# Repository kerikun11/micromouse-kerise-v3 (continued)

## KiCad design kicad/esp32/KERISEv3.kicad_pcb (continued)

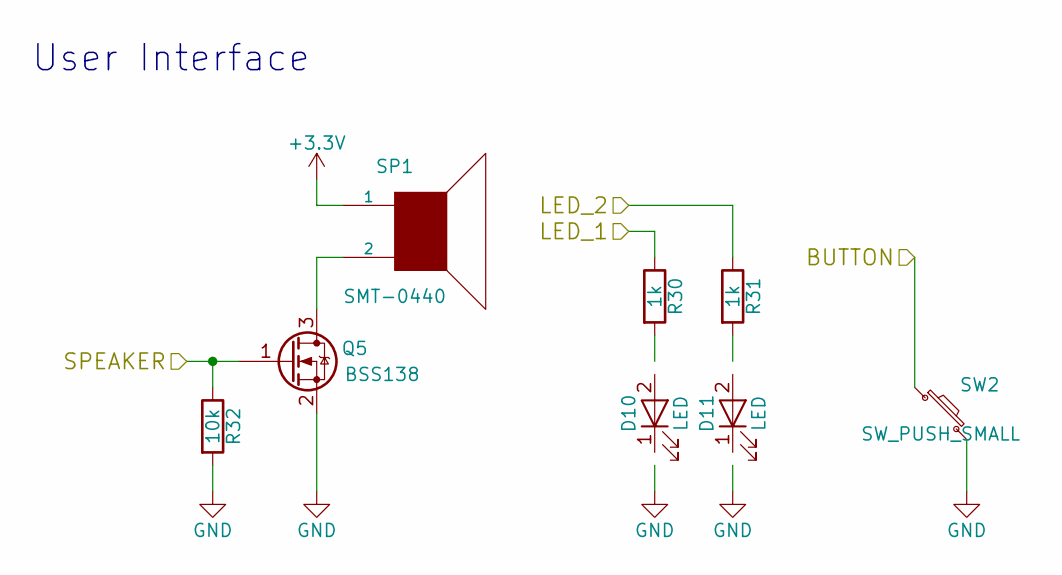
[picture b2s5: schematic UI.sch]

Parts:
D10, D11: LED; LED_0402
Q5: BSS138; SOT-23
R30, R31: 1k; R_0201
R32: 10k; R_0201
SP1: SMT-0440; SMT-0440-S-R
SW2: SW_PUSH_SMALL; SW_SPST_KMR2

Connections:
+3V3: SP1.1; also elsewhere on the board
BUTTON: SW2.1; also elsewhere on the board
GND: Q5.2 (S), R32.2, SW2.2; also elsewhere on the board
unnamed: Q5.1 (G), R32.1
unnamed 80: Q5.3 (D), SP1.2; also elsewhere on the board

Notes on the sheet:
User Interface

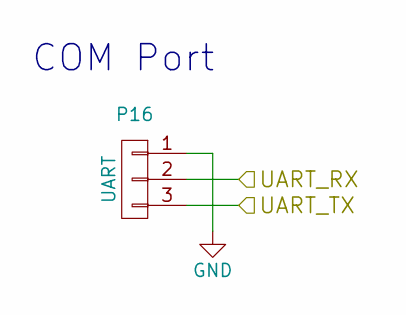
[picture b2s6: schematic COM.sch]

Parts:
P16: UART; JST_SH_BM03B-SRSS-TB_03x1.00mm_Straight

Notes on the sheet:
COM Port

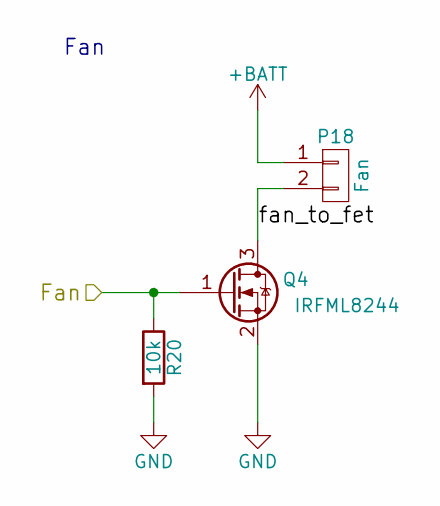
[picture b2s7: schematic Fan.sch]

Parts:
P18: Fan; SMD_conn_2
Q4: IRFML8244; SOT-23
R20: 10k; R_0201

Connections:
+BATT: P18.1; also elsewhere on the board
/Fan/fan_to_fet: P18.2, Q4.3 (D)
FAN: Q4.1 (G), R20.1; also elsewhere on the board
GND: Q4.2 (S), R20.2; also elsewhere on the board

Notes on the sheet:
Fan

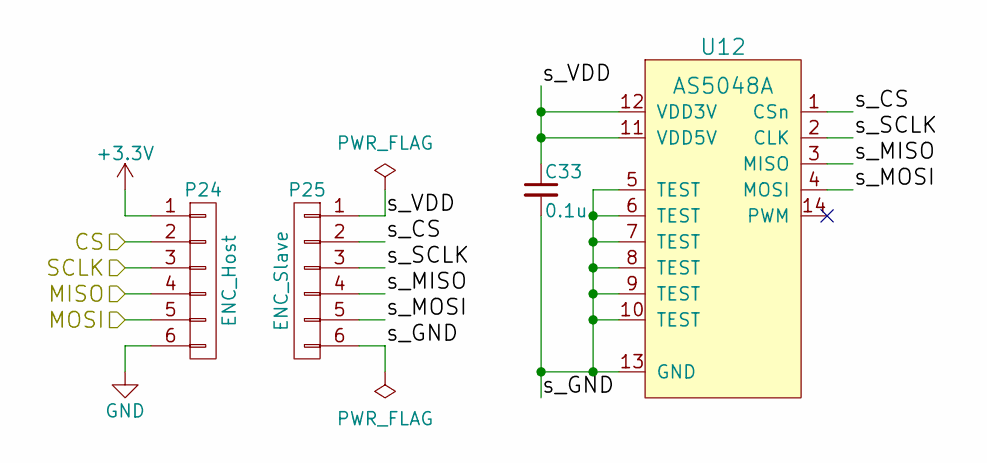
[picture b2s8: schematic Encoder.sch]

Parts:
C26: 0.1u; C_0201
P19: ENC_Host; STAND_AS_HOST
P20: ENC_Slave; STAND_AS_SLAVE
U8: AS5048A; TSSOP-14_4.4x5mm_Pitch0.65mm

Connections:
+3V3: P19.1; also elsewhere on the board
/Encoder_R/s_CS: P20.2, U8.1 (CSn)
/Encoder_R/s_GND: C26.2, P20.6, U8.5 (TEST), U8.6 (TEST), U8.7 (TEST), U8.8 (TEST), U8.9 (TEST), U8.10 (TEST), U8.13 (GND)
/Encoder_R/s_MISO: P20.4, U8.3 (MISO)
/Encoder_R/s_MOSI: P20.5, U8.4 (MOSI)
/Encoder_R/s_SCLK: P20.3, U8.2 (CLK)
/Encoder_R/s_VDD: C26.1, P20.1, U8.11 (VDD5V), U8.12 (VDD3V)
ENC-CHAIN: P19.4; also elsewhere on the board
GND: P19.6; also elsewhere on the board
SPI-CS-ENC: P19.2; also elsewhere on the board
SPI-MOSI: P19.5; also elsewhere on the board
SPI-SCLK: P19.3; also elsewhere on the board

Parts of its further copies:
C33: 0.1u; C_0201
P24: ENC_Host; STAND_AS_HOST
P25: ENC_Slave; STAND_AS_SLAVE
U12: AS5048A; TSSOP-14_4.4x5mm_Pitch0.65mm

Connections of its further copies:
+3V3: P24.1; also elsewhere on the board
/Encoder_L/s_CS: P25.2, U12.1 (CSn)
/Encoder_L/s_GND: C33.2, P25.6, U12.5 (TEST), U12.6 (TEST), U12.7 (TEST), U12.8 (TEST), U12.9 (TEST), U12.10 (TEST), U12.13 (GND)
/Encoder_L/s_MISO: P25.4, U12.3 (MISO)
/Encoder_L/s_MOSI: P25.5, U12.4 (MOSI)
/Encoder_L/s_SCLK: P25.3, U12.2 (CLK)
/Encoder_L/s_VDD: C33.1, P25.1, U12.11 (VDD5V), U12.12 (VDD3V)
ENC-CHAIN: P24.5; also elsewhere on the board
GND: P24.6; also elsewhere on the board
SPI-CS-ENC: P24.2; also elsewhere on the board
SPI-MISO: P24.4; also elsewhere on the board
SPI-SCLK: P24.3; also elsewhere on the board

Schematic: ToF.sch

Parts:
C27: 4.7u; C_0402
C28: 0.1u; C_0201
P21: ToF_Host; STAND_PR_HOST
P22: ToF_Slave; STAND_PR_SLAVE
R21, R22: 4.7k; R_0201
U9: VL53L0X

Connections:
+3V3: P21.1; also elsewhere on the board
/ToF/s_3.3V: C27.1, C28.1, P22.1, R21.1, R22.1, U9.1 (AVDDVCSEL), U9.5 (XSHUT), U9.11 (AVDD)
/ToF/s_GND: C27.2, C28.2, P22.4, U9.2 (AVSSVCSEL), U9.3 (GND), U9.4 (GND2), U9.6 (GND3), U9.12 (GND4)
/ToF/s_SCL: P22.3, R22.2, U9.10 (SCL)
/ToF/s_SDA: P22.2, R21.2, U9.9 (SDA)
GND: P21.4; also elsewhere on the board
I2C-SCL: P21.3; also elsewhere on the board
I2C-SDA: P21.2; also elsewhere on the board

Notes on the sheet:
ToF

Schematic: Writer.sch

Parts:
C29, C31: 0.1u; C_0402
C30, C32: 4.7u; C_0402
D9: Status; LED_0402
F1: FEMTOSMDC035F-02; R_0603
J1: USB_OTG; ZX62R-B-5P
P23: COM; Socket_Strip_Straight_1x04_Pitch1.27mm
R23: 4.7k; R_0402
R24: 10k; R_0402
U10: MCP73831; SOT-23-5
U11: FT234XD; DFN-12-1EP_3x3mm_Pitch0.45mm

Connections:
/Writer/BAT_OUT: C32.1, P23.1, U10.3 (VBAT)
/Writer/USB_5V: C29.1, C30.1, D9.2 (A), F1.2, U10.4 (VDD), U11.4 (VCC)
/Writer/USB_BUS: F1.1, J1.1 (VBUS)
/Writer/USB_D+: J1.3 (D+), U11.12 (USBDP)
/Writer/USB_D-: J1.2 (D-), U11.1 (USBDM)
/Writer/USB_GND: C29.2, C30.2, C31.2, C32.2, J1.5 (GND), J1.6 (Shield), P23.2, R23.2, U10.2 (VSS), U11.5 (GND), U11.13 (GND)
/Writer/USB_RX: P23.4, U11.10 (RXD)
/Writer/USB_TX: P23.3, U11.7 (TXD)
unnamed: C31.1, U11.2 (RESET#), U11.3 (3V3OUT), U11.9 (VCCIO)
unnamed: D9.1 (K), R24.1
unnamed: R23.1, U10.5 (PROG)
unnamed: R24.2, U10.1 (STAT)

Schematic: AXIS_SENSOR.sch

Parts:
C34, C35: 0.1u; C_0201
U13: ICM-20602; LGA-16-3x3

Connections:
+3V3: C34.1, U13.1 (VDDIO), U13.16 (VDD); also elsewhere on the board
GND: C34.2, C35.2, U13.8 (FSYNC), U13.9 (RESV), U13.10 (RESV), U13.11 (RESV), U13.12 (RESV), U13.13 (GND), U13.15 (RESV); also elsewhere on the board
unnamed: C35.1, U13.14 (REGOUT)
SPI-CS-AXIS: U13.5 (CS); also elsewhere on the board
SPI-MISO: U13.4 (SA0/SDO); also elsewhere on the board
SPI-MOSI: U13.3 (SDA/SDI); also elsewhere on the board
SPI-SCLK: U13.2 (SCL/SPC); also elsewhere on the board

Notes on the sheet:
AXIS Sensor

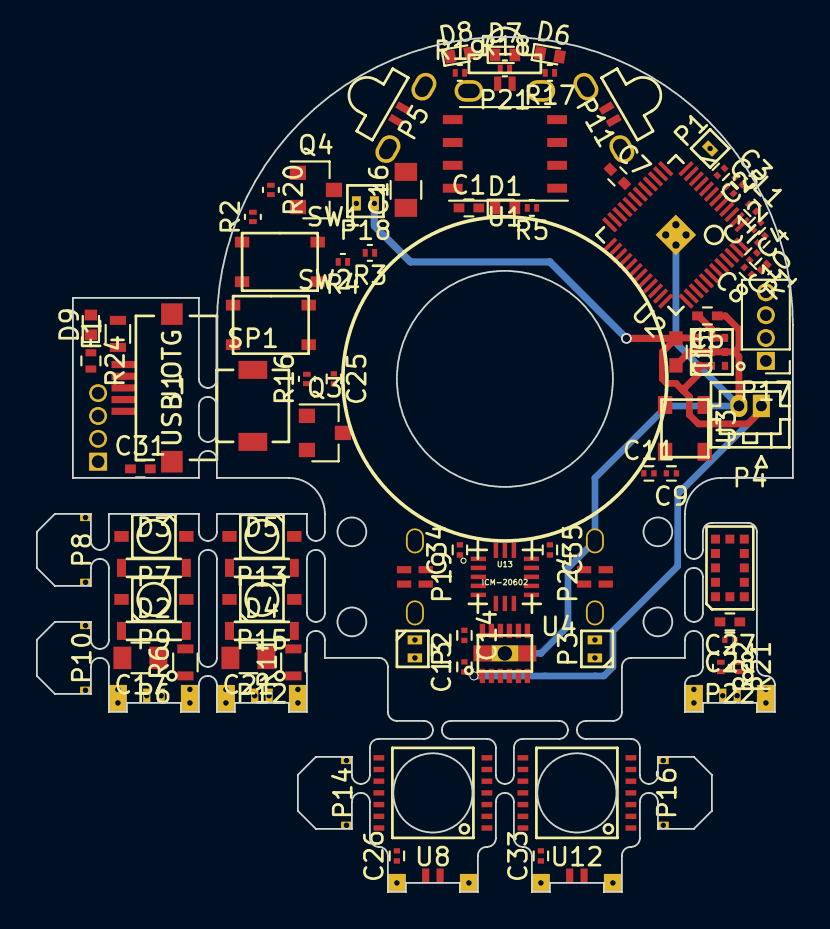
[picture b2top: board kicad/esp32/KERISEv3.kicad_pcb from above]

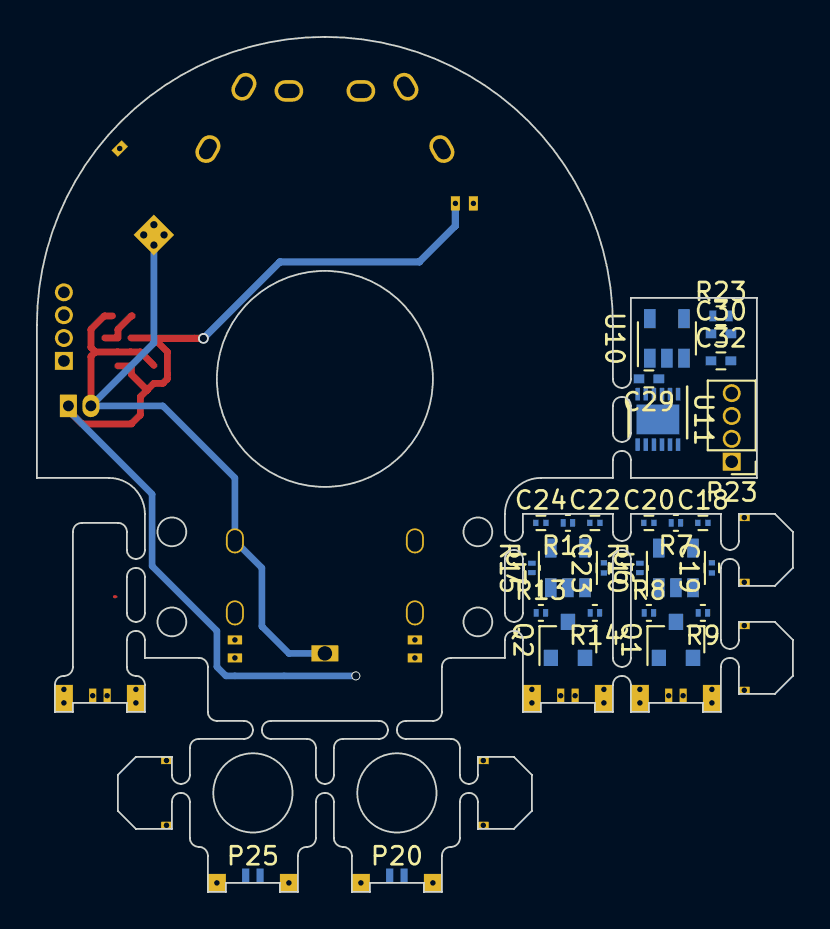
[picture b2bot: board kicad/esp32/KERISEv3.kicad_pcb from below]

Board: 2 copper layers, 42.0 x 47.5 mm, 116 parts (27 on the bottom side), 101 nets.

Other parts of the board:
C25: 0.1u; C_0201
D6, D7, D8: LED; LED_0402
P17: COM; Pin_Header_Straight_1x04_Pitch1.27mm
Q3: IRFML8244; SOT-23
R16, R17, R18, R19: 1k; R_0201

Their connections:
+BATT: P17.1; also elsewhere on the board
GND: D6.1, D7.1, D8.1, P17.2, Q3.2; also elsewhere on the board
LED_1: R17.1; also elsewhere on the board
LED_2: R18.1; also elsewhere on the board
LED_3: R19.1; also elsewhere on the board
unnamed: C25.1, R16.2
unnamed: C25.2, Q3.3
unnamed: D6.2, R17.2
unnamed: D7.2, R18.2
unnamed: D8.2, R19.2
unnamed 80: R16.1; also elsewhere on the board
SPEAKER: Q3.1; also elsewhere on the board
UART-RX: P17.3; also elsewhere on the board
UART-TX: P17.4; also elsewhere on the board

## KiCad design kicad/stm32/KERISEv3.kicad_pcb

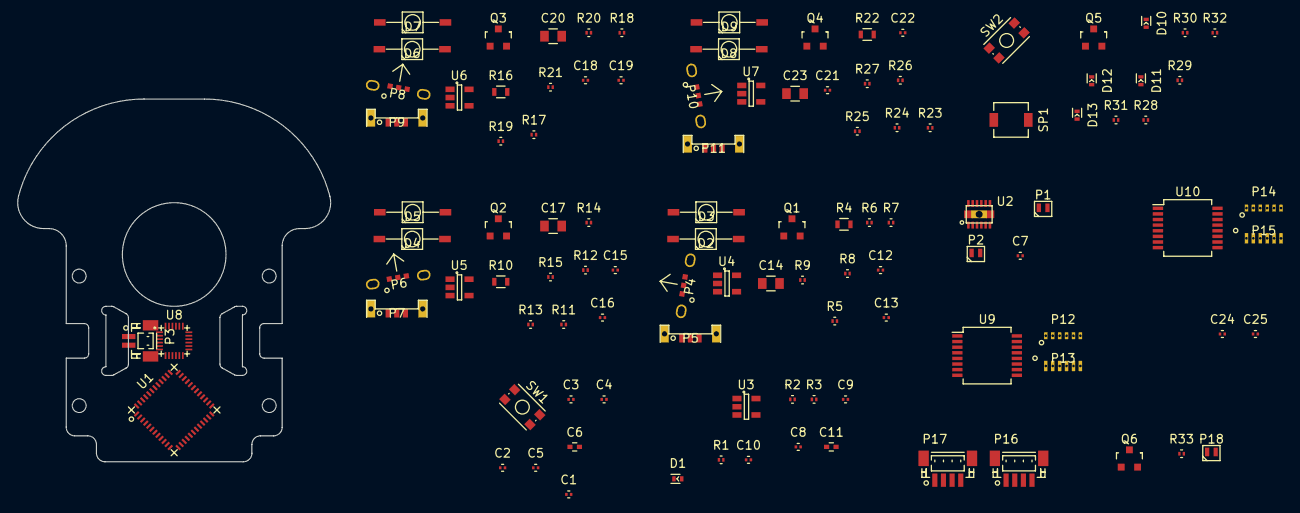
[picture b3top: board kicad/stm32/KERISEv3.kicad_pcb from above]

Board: 2 copper layers, 36.2 x 42.0 mm, 108 parts (0 on the bottom side), 99 nets, no tracks yet.

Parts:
C1, C2, C3, C4, C5, C7, C8, C10, C24, C25: 0.1u; C_0201
C6: 4.7uF; C_0402
C9, C13, C16, C19, C22: 0.01u; C_0201
C11: 4.7u; C_0402
C12, C15, C18, C21: 22p; C_0201
C14, C17, C20, C23: 47u; C_0805
D1: Power; LED_0402
D2, D4, D6, D8: VEMD2020X01; VISHAY_DIODE
D3, D5, D7, D9: VSMB294008G; VISHAY_DIODE
D10, D11, D12, D13: LED; LED_0402
P1: Motor_L; SMD_conn_2
P2: Motor_R; SMD_conn_2
P3: Battery; JST_SH_BM02B-SRSS-TB_02x1.00mm_Straight
P4, P6, P8, P10: PR_Host; STAND_PR_HOST
P5, P7, P9, P11: PR_Slave; STAND_PR_SLAVE
P12, P14: ENC_Host; STAND_AS_HOST
P13, P15: ENC_Slave; STAND_AS_SLAVE
P16: SWD; JST_SH_BM04B-SRSS-TB_04x1.00mm_Straight
P17: UART; JST_SH_BM04B-SRSS-TB_04x1.00mm_Straight
P18: Fan; SMD_conn_2
Q1, Q2, Q3, Q4, Q6: IRFML8244; SOT-23
Q5: BSS138; SOT-23
R1, R2, R3, R6, R7, R12, R13, R18, R19, R24, R25, R28, R29, R30, R31: 1k; R_0201
R4, R10, R16, R22: 100; R_0603
R5, R11, R17, R23: 220k; R_0201
R8, R14, R20, R26: 100k; R_0201
R9, R15, R21, R27, R32, R33: 10k; R_0201
SP1: SMT-0440; SMT-0440-S-R
SW1: RESET; SW_SPST_KMR2
SW2: SW_PUSH_SMALL; SW_SPST_KMR2
U1: STM32F411CEU6; QFN-48-1EP_7x7mm_Pitch0.5mm
U2: DRV8835
U3: NJM12888; SOT-23-5
U4, U5, U6, U7: AD8601; SOT-23-5
U8: MPU6500; QFN-24-1EP_3x3mm_Pitch0.4mm
U9, U10: AS5145; SSOP-16_5.3x6.2mm_Pitch0.65mm

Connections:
+3V3: C1.2, C2.2, C3.2, C4.2, C7.1, C10.1, C11.1, C24.2, P4.1, P6.1, P8.1, P10.1, P12.1, P14.1, R2.1, SP1.1, U1.1, U1.24, U1.36, U1.48, U2.12, U3.5, U8.8, U8.13
+BATT: C8.1, P3.1, P17.1, P18.1, R1.1, U2.1, U3.1, U3.3
/AXIS_SENSOR/AXIS_CAP: C25.1, U8.10
/ENC_L/MISO: P12.5, P14.4
/ENC_L/s_3.3V: P13.1, U9.15, U9.16
/ENC_L/s_CSn: P13.6, U9.11
/ENC_L/s_MISO: P13.5, U9.9
/ENC_L/s_MOSI: P13.4, U9.8
/ENC_L/s_SCLK: P13.3, U9.10
/ENC_L/s_VSS: P13.2, U9.7
/ENC_R/s_3.3V: P15.1, U10.15, U10.16
/ENC_R/s_CSn: P15.6, U10.11
/ENC_R/s_MISO: P15.5, U10.9
/ENC_R/s_MOSI: P15.4, U10.8
/ENC_R/s_SCLK: P15.3, U10.10
/ENC_R/s_VSS: P15.2, U10.7
/FR_SL/LED_to_C: C14.1, D3.2, R4.2
/FR_SL/LED_to_FET: D3.1, Q1.3
/FR_SL/s_3.3V: D2.1, P5.1, R4.1, R6.1, U4.5
/FR_SL/s_GND: C14.2, P5.4, Q1.2, R7.2, R8.2, R9.2, U4.2
/FR_SL/s_IR_LED: P5.2, Q1.1, R9.1
/FR_SL/s_IR_RCV: C12.1, P5.3, R5.1, U4.1
/IR_RCV_FL/LED_to_C: C17.1, D5.2, R10.2
/IR_RCV_FL/LED_to_FET: D5.1, Q2.3
/IR_RCV_FL/s_3.3V: D4.1, P7.1, R10.1, R12.1, U5.5
/IR_RCV_FL/s_GND: C17.2, P7.4, Q2.2, R13.2, R14.2, R15.2, U5.2
/IR_RCV_FL/s_IR_LED: P7.2, Q2.1, R15.1
/IR_RCV_FL/s_IR_RCV: C15.1, P7.3, R11.1, U5.1
/IR_RCV_FR/LED_to_C: C20.1, D7.2, R16.2
/IR_RCV_FR/LED_to_FET: D7.1, Q3.3
/IR_RCV_FR/s_3.3V: D6.1, P9.1, R16.1, R18.1, U6.5
/IR_RCV_FR/s_GND: C20.2, P9.4, Q3.2, R19.2, R20.2, R21.2, U6.2
/IR_RCV_FR/s_IR_LED: P9.2, Q3.1, R21.1
/IR_RCV_FR/s_IR_RCV: C18.1, P9.3, R17.1, U6.1
/IR_RCV_SR/LED_to_C: C23.1, D9.2, R22.2
/IR_RCV_SR/LED_to_FET: D9.1, Q4.3
/IR_RCV_SR/s_3.3V: D8.1, P11.1, R22.1, R24.1, U7.5
/IR_RCV_SR/s_GND: C23.2, P11.4, Q4.2, R25.2, R26.2, R27.2, U7.2
/IR_RCV_SR/s_IR_LED: P11.2, Q4.1, R27.1
/IR_RCV_SR/s_IR_RCV: C21.1, P11.3, R23.1, U7.1
/Motor/MT_OUT_L1: P1.1, U2.2
/Motor/MT_OUT_L2: P1.2, U2.3
/Motor/MT_OUT_R1: P2.1, U2.4
/Motor/MT_OUT_R2: P2.2, U2.5
AXIS_INT: U1.21, U8.12
AXIS_MISO: U1.27, U8.9
AXIS_MOSI: U1.28, U8.24
AXIS_SCK: U1.26, U8.23
AXIS_~CS: U1.25, U8.22
BAT-VOL: R1.2, R3.1, U1.17
BUTTON: SW2.1, U1.2
ENC_MISO: P14.5, U1.16
ENC_SCK: P12.3, P14.3, U1.15
ENC_~CS: P12.6, P14.6, U1.14
FAN: Q6.1, R33.1, U1.45
GND: C1.1, C2.1, C3.1, C4.1, C5.1, C6.1, C7.2, C8.2, C9.2, C10.2, C11.2, C24.1, C25.2, D1.1, D10.1, D11.1, D12.1, D13.1, P3.2, P4.4, P6.4, P8.4, P10.4, P12.2, P12.4, P14.2, P16.2, P17.2, Q5.2, Q6.2, R3.2, R32.2, R33.2, SW1.2, SW2.2, U1.8, U1.23, U1.35, U1.44, U1.47, U2.6, U2.11, U2.13, U3.2, U8.11, U8.18, U8.20
LED_1: R28.1, U1.3
LED_2: R29.1, U1.4
LED_3: R30.1, U1.5
LED_4: R31.1, U1.6
MT-IN-L1: U1.29, U2.10
MT-IN-L2: U1.30, U2.9
MT-IN-R1: U1.31, U2.8
MT-IN-R2: U1.32, U2.7
unnamed: C6.2, U1.22
unnamed: C9.1, U3.4
unnamed: C12.2, C13.1, R5.2, U4.4
unnamed: C13.2, D2.2, R8.1
unnamed: C15.2, C16.1, R11.2, U5.4
unnamed: C16.2, D4.2, R14.1
unnamed: C18.2, C19.1, R17.2, U6.4
unnamed: C19.2, D6.2, R20.1
unnamed: C21.2, C22.1, R23.2, U7.4
unnamed: C22.2, D8.2, R26.1
unnamed: D1.2, R2.2
unnamed: D10.2, R28.2
unnamed: D11.2, R29.2
unnamed: D12.2, R30.2
unnamed: D13.2, R31.2
unnamed: P18.2, Q6.3
unnamed: Q5.3, SP1.2
unnamed: R6.2, R7.1, U4.3
unnamed: R12.2, R13.1, U5.3
unnamed: R18.2, R19.1, U6.3
unnamed: R24.2, R25.1, U7.3
PR-LED-FL: P6.2, U1.41
PR-LED-FR: P8.2, U1.18
PR-LED-SL: P4.2, U1.40
PR-LED-SR: P10.2, U1.19
PR-RCV-FL: P6.3, U1.11
PR-RCV-FR: P8.3, U1.12
PR-RCV-SL: P4.3, U1.10
PR-RCV-SR: P10.3, U1.13
RESET: C5.2, P16.4, SW1.1, U1.7
SPEAKER: Q5.1, R32.1, U1.46
SWCLK: P16.1, U1.37
SWDIO: P16.3, U1.34
UART-RX: P17.3, U1.43
UART-TX: P17.4, U1.42

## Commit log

2017-02-16 基板の作成開始
2017-02-19 自動配線成功
2017-03-06 ファームウェアを追加
2017-03-08 MPU6500の動作確認
2017-03-12 リフレクタの読み取りコードを実装
2017-03-12 3Dデータの追加
2017-03-13 2つのADCを同時サンプリング
2017-03-13 externを各ファイルに書くように変更．LEDクラスを作成
2017-03-13 タスク生成時にコアを選べるように変更
2017-03-16 UIを拡充
    ブザー，ボタン，LED
2017-03-21 SPIをESP-IDFからArduinoへ一時退避
    ESP-IDFのSPIだとクラッシュするので仕方なくArduinoのSPIに退避
2017-03-21 ESP32の回路図を更新
    BOOTに必要なピンを明記
2017-03-23 MazeSolverを追加
2017-03-23 速度算出に加速度を併用．PIDパラメータの選定
2017-04-03 実際に使用している3Dモデル
2017-04-07 軽く動く
2017-04-09 UIを拡充，安定性の向上
2017-04-15 展示用に速度を抑えて安定走行
2017-04-16 軌道生成用のMATLABコードを追加
2017-04-16 最短走行の角度を30度から45度の倍数に変更
    マウスが小さくなったから45度でOK
2017-04-16 パラメータの調整
2017-04-20 SPIをESP-IDFのライブラリに変更
    ライブラリアップデートによりクラッシュしなくなったので．
2017-04-24 割と速いパラメータ
    look_aheadを20にしたら，高速走行が可能になった．
    カーブを曲がるときは既定の速度で曲がるのではなく，現在の速度で曲がるように変更．ステップ入力がなくなった．
    速度コントローラのPIDゲインが大きすぎるからか，加速のときによくクラッシュする．
2017-05-04 ゆっくりにしないと滑る
2017-05-06 MoveActionをFastRunとSearchRunに分割
2017-05-07 一時退避していたMazeSolverの中身を実装
    ※ときどきバックしだすバグあり
2017-06-04 曲がるときにファンを回して滑らないように
2017-06-04 速度選択のUIを作成
2017-06-05 自作の迷路探索アルゴリズムを適用
2017-06-07 背中の壁当ての座標バグを修正
2017-06-07 addし忘れていたファイルを追加
2017-06-11 マウス合宿パラメータ
2017-06-13 自作迷路パラメータ，ちょい攻め
2017-06-21 2輪の基板を作成
    部品を配置
2017-06-21 壁センサの光量を上げて，区画ごとに止まらずに探索可能に
2017-06-21 データシートを追加
2017-06-21 STM32のKiCadファイルを削除
2017-06-25 部品の配置と電源ラインの引き方を変更．
    センサ部分にノイズがはいらないように考慮
2017-06-25 スタートのオフセット位置を考えて表示を回転する機能を追加
    45度から始まるカーブなどが設計しやすくなった
2017-07-09 配線を0.15mmにして自動配線成功
2017-07-12 Elecrowに指摘された部分を修正
    発注基板
2017-07-12 最初の直線を変数にして管理
2017-07-13 入力パラメータの定義を変更，わかりやすくした
2017-07-17 エンコーダの位置を修正，自動配線完了
2017-07-18 3.3Vの電源ラインを強化，変換基板を付属
2017-07-18 自動配線を適用
2017-07-20 4輪の改良版を設計
2017-07-22 部品を配置
2017-07-27 4輪改良版自動配線完了
2017-07-28 細部を改良，自動配線成功
2017-08-03 Elecrowからのリジェクトを修正
2017-08-21 部品を配置
    壁センサだけ自動配線
2017-08-21 配線完了
2017-08-21 細部の修正
2017-08-24 3Dデータファイルを追加
    Fusion360から吐き出したもの．実際にKERISEv3で使われているもの
2017-08-25 マスクの表裏ミスを修正
2017-08-25 put_backでフリーズするバグを修正
    delete_task()をせずに，enabledフラグを設置
2017-09-15 軌道生成コードにコメントを挿入
    ブログに載せるため
2017-09-15 KiCadファイルを追加
    KERISEv3-2 発注版
2017-09-15 フットプリントのミスを修正
2017-09-21 フットプリントを改良，アナログ電源を分離
2017-09-24 回路とフットプリントを改良
2017-09-24 各種機能テスト用ファームウェアを追加
2017-09-24 ギアのDXFファイルを追加
2017-10-01 M0.3のギアに変更した機体でパラメータ調整
2017-10-10 リフレクタのコードを改良，工大祭2017パラメータ
    割と安定走行
2017-10-10 リフレクタを2レンジに変更
    壁検出用(強)と壁制御用(弱)
    wall_avoidをenable(試験的)
2017-10-11 リフレクタのテスト用コードを追加
2017-10-17 自動配線1残し
2017-10-17 自動配線を適用，ロゴを追加
2017-10-19 前壁補正を調整，最短にバグあり
    探索走行は割と安定
    しかし，最短走行の速度がなぜか早くなるバグあり，不安定
2017-10-19 リフレクタサンプルコードを更新，ワンショット機能，省エネ
2017-10-19 新リフレクタライブラリに対応したWallDetectorの構築
2017-10-21 新リフレクタ&壁ライブラリを適用，未動作確認
    コンパイルエラーをベースに適用
2017-10-24 最短走行終了時にフリーズするバグ修正，安定走行
    delete_task();が早すぎた．
    壁制御を調整
    壁補正を調整
2017-10-26 走行パラメータ調整
2017-10-26 KERISEv3からファームウェアを移植，各種動作確認用プログラムを追加
2017-10-27 I/Oピンの定義をconfig.hにまとめた
2017-10-27 実装経験をもとにフットプリントを改良，ミスを修正
    SC70サイズのオペアンプのピンアサインを修正
2017-10-27 BLEの送信クラスを追加
2017-10-27 モーターとエンコーダの動作を確認
2017-10-27 KERISEv3のコードのMPUをICM，AS4145をAS5048Aに変更
2017-10-27 ToFとBLEのコードを追加
    未初期化
2017-10-28 複数デバイスで使用しているSPIバスの初期化をbeginの引数で選択するように変更
2017-10-28 mouseにToFとBLEを追加，未動作確認
2017-10-29 エンコーダの値が飛ぶバグを修正，ICM20602のキャリブレーション方法を改良
    AS5048AはSCLKがCSと同時に下がると1クロック目が失われる仕様がある．
    それを回避するために，CSをdigitalWrite()でやっていたが，これがICM20602との通信と衝突していた可能性がある．
    SPI前後のコールバック関数内でdigitalWrite()をすることで解決．
    ICM20602のキャリブレーションを2秒1回ではなく，500ms4回にすることで精度が飛躍的に向上
2017-10-29 BLE.begin()でassertするバグを修正，ToFの読み値をBLEで送るコードの追加
    WiFi.mode(WIFI_OFF);が邪魔をしていた
2017-10-29 各種テストコードの移植，ジャイロの係数の更新
    機体を10周手で回して，角度の積算をみて係数を更新．結構違った．
2017-10-30 モーターの配線ミスをソフトで修正！！宴会芸でPIDチューニング
    モーターが左右逆に取り付けてあった．ピン定義を入れ替えて対応
2017-11-01 迷路をSPIFFSに保存するサンプルプログラム
2017-11-02 ジャイロの係数を間違えて加速度にかけていたミスを修正
2017-11-02 ICM-20602の内蔵ローパスフィルタを有効化
2017-11-02 モーターを回すとICMのジャイロにノイズが入るバグを特定したコード
2017-11-03 速度制御パラメータを改変，これから調整
2017-11-04 enabledフラグ周りを改良
2017-11-05 ICM-20602を交換してなんとか動作
2017-11-05 クラス名を一般化．型番ではなく役割に
    今後は役割にして，型番のドライバクラスを継承したい
2017-11-05 不揮発性メモリへの保存機能を追加
2017-11-05 spi.inoのコードを更新
    AxisとEncoderに統一
2017-11-05 SPIピンの定義方法を変更
    デバイスごとに定義
2017-11-05 MPU6500とAS5145のクラス名をAxisとEncoderに変更
    今後の移植性のため
2017-11-05 Mazeクラスを整理
2017-11-05 PIDチューニング，まあまあ
2017-11-06 ToFを追加
2017-11-06 最短でゴールについた後にクラッシュするバグを修正．
    vTaskDelayUntilは呼ばない間の分が連続で呼ばれることが分かった
2017-11-06 xLastWakeTimeの初期化を1行で行う
    見やすく
2017-11-06 ToFによる曲がる前の前壁補正
2017-11-07 ESP32のPreferemcesに前壁パラメータを保存
2017-11-07 壁切れの実装，前壁補正，割といい感じ
2017-11-08 前壁キャリブレーション機能を追加
2017-11-08 横壁補正を調整，ちょっといい感じ．
    最短にも横壁補正を入れた．
    壁切れはエラーが多いので一時停止
2017-11-08 ゲイン調整，なんとか動いた
2017-11-11 横壁補正のゲインを一定に．
2017-11-12 車輪の径を更新，最短に壁切れを追加，Position::rotate()の仕様変更
2017-11-13 インターフェースを更新，最短走行の壁制御を選択できるように
2017-11-13 横壁制御に飽和を追加，いい感じ
2017-11-13 横壁制御を端的なものに復帰
2017-11-14 utils.hファイルを一時的に作成
    コードを見やすく
2017-11-14 utils.cppを作成
    ヘッダファイルにCコードを書くのはよくない
2017-11-14 軌道を改良
    最新の直観に基づく
2017-11-14 軌道のバグ修正
    配列の個数の定義を間違えていた
2017-11-16 複数区画がゴールだとAgent::reset()したときにREACHED_START状態にならないバグを修正
2017-11-16 最新の探索器に更新
2017-11-16 最短走行に小回り90度を追加，斜めなしモード
    斜め走行がないモードを生成
2017-11-16 最短小回り90度の軌道生成コードを追加
2017-11-16 直線制御の終端速度を関数を抜けるタイミングで達成できるように変更
2017-11-17 全日本前日パラメータ
2017-11-18 ファンの回転数を変える機能を搭載
2017-11-18 ハーフ決勝用にゴールと時間を設定
2017-11-18 ゴールと探索終了時に一度止まって迷路をSPIFFSに保存
2017-11-18 横壁キャリブレーションはスタート時にせず，あらかじめ行っておくように変更
2017-11-18 前壁補正，ターン，既知区間スピードの調整
2017-11-19 全日本マイクロマウス2016パラメータ
2017-11-24 ログファイルを追加
2017-11-24 ゴール区画座標を練習用へ変更
2017-11-29 3Dモデルを追加
    TEPとFusion360ファイルの両方をエクスポート
2017-12-01 ToFの測定コードを改良
    測定に失敗したときはpassed_msをクリアしない
2017-12-01 FastRunのターンにフィードフォワード項を入れて高速化
2017-12-04 AxisをIMUに名前変更
2017-12-04 debug.h を ExternalController.hに変更
2017-12-04 依存関係の整理
    不要なincludeを削除
    UserInterface.hの分割
2017-12-04 UserInterface.hを新たに生成
    マウスが持つあらゆるセンサを活用したUI
2017-12-04 探索のターンにもフィードフォワード項を追加
    探索スピードを上げることができた
2017-12-06 壁制御の調整
2017-12-07 壁センサの基準値保存をPreferencesではなくSPIFFSに保存
    管理をしやすくするため
2017-12-07 速度コントローラのコードを改良
    Accumulatorクラスを作成
2017-12-11 スタート時に前壁を作るバグを修正
    スタート前が直線のときToFの計測ができず，古いデータにより前壁ができていた．
2017-12-11 斜めの壁切れを導入
2017-12-11 スタート時に前壁を作るバグの再修正
    別のアプローチ
2017-12-22 プチコン用にスピードを調整
2018-01-01 機体を振ってモード選択する機能を実装
2018-01-07 新しいTaskBaseを導入
2018-01-09 TaskBaseを更新
    要動作確認！
2018-01-10 加速度の単位を修正
2018-01-10 グローバル変数の宣言をglobal.cppに集約
    global.cpp
    global.h
    を新規作成し，グローバル変数を管理
    ライブラリをよりライブラリらしくした
2018-01-14 リフレクタのバグを修正
    飽和の方向が間違っていた
2018-01-21 RTOSのスタックサイズと優先度をマクロで定義
    他のコードと統一的に
2018-01-23 エンコーダ偏心補正の実験コードを追加
2018-03-01 小さな改良
2018-03-28 SPIFFSへの書き込みに時間がかかるので，待つ．
2018-04-01 直線加速の新探索アルゴリズムを適用
2018-04-01 TaskBaseのバグを修正
2018-04-01 移動中に計算処理を行う新探索アルゴリズムを適用
2018-04-03 迷路のバックアップ方式を変更，ログを残す
2018-04-03 バックアップコードを改良
2018-04-04 パラメータ調整
2018-04-04 袋小路でバックアップ
2018-04-05 動作確認用のコードを最新のmouseを基に更新
2018-04-05 Accumulator.hを導入
2018-04-05 軌道を更新
2018-04-05 KERISEv5の変更点を反映
2018-04-08 xLastWakeTimeの更新位置を変更
2018-04-08 Agent.hを導入
2018-04-12 ゴール区画を設定する機能
2018-04-13 宴会芸モードを追加
2018-04-15 曲線減速の導入，未完成
2018-04-17 AccelDesignerを追加
2018-04-18 MazeLibのバグを修正
2018-04-20 曲線デザイナを追加
2018-04-25 コードを改良
2018-04-25 cbrtのバグを修正
2018-04-26 コメントを改良
2018-05-01 calcVelocityEnd()のバグを修正
2018-05-25 MazeLibのcalcNextDirs()を更新
2018-05-26 第2回プチコンコード
2018-07-13 I2CをESP-IDFのものに変更
2018-08-17 strict char case
2018-08-22 ESP-IDFに移行，未動作確認
2018-08-22 set baudrate to 2000000 bps
2018-08-22 add arduino config
2018-08-22 srcをフォルダ分け
2018-08-22 update indent
2018-08-23 i2c.h および spi.h を導入
2018-08-24 update mazelib
2018-08-25 rm Logger, format, fail safe
2018-08-25 update WallDetector format and distance, fix warnnigs
2018-08-25 git submodule add MazeLib
2018-08-30 ToFの接触不良を修正
2018-08-31 速度を早めたらなんか動いた
2018-09-01 探索速度を調整 東日本地区大会2018
2018-09-02 練習用ゴールに設定
2020-05-05 add gitignore
2021-01-11 update directory structure
2021-01-11 update MazeLib repo URL
